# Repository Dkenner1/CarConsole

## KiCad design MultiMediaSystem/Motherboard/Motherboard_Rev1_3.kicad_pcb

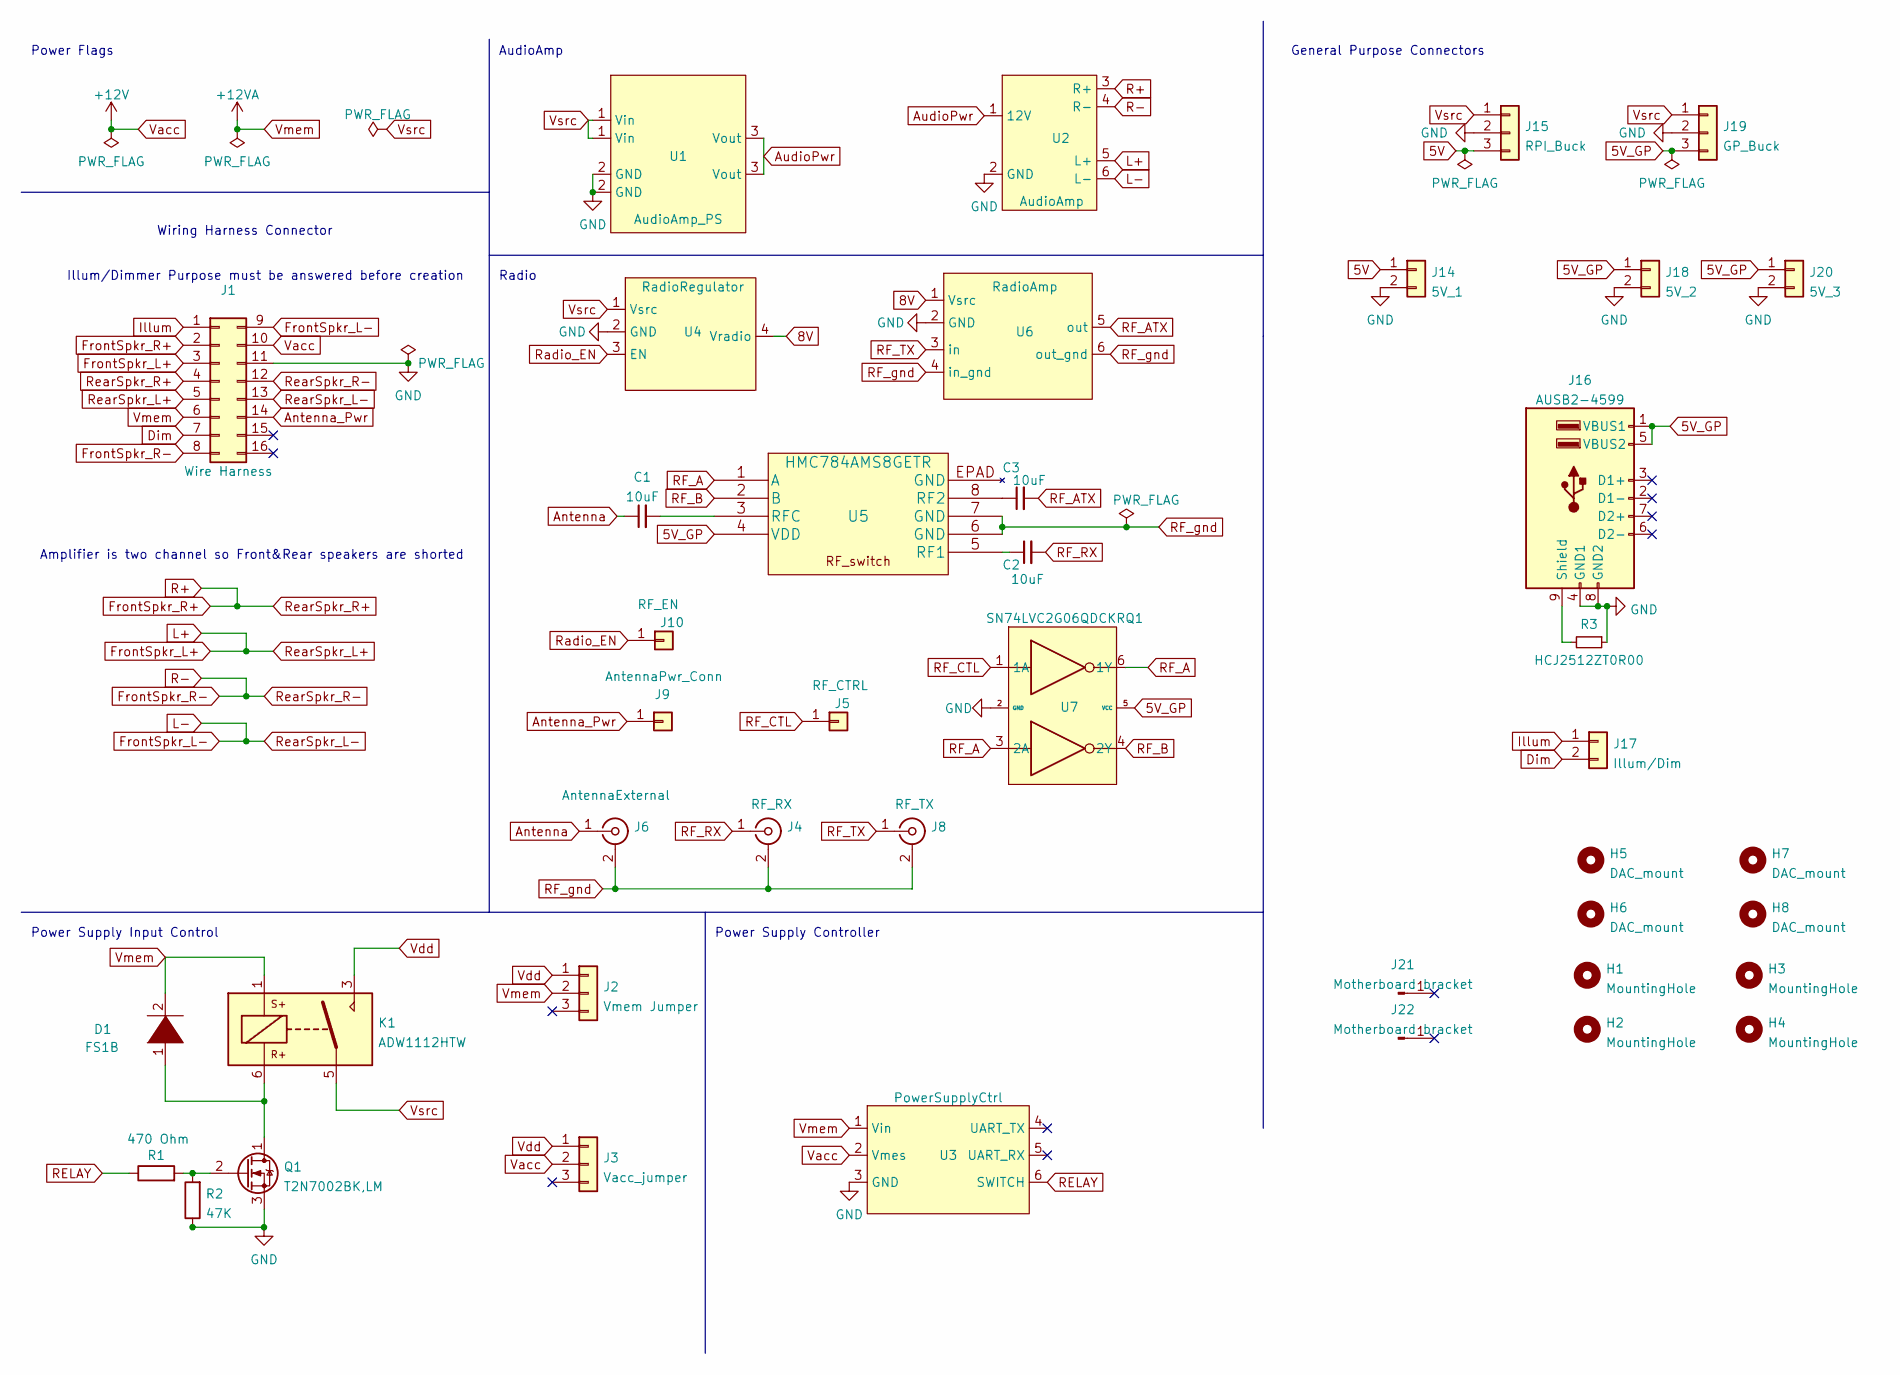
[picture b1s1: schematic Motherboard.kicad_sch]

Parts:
C1, C2, C3: 10uF; C_0603_1608Metric_Pad1.08x0.95mm_HandSolder
D1: FS1B; D_SOD-123F
H1, H2, H3, H4: MountingHole; RectangleSlot
H5, H6, H7, H8: DAC_mount; MountingHole_2.5mm_Pad
J1: Wire Harness; HeadUnit_Conn
J2: Vmem Jumper; PinHeader_1x03_P2.54mm_Vertical
J3: Vacc_jumper; PinHeader_1x03_P2.54mm_Vertical
J4: RF_RX; SMA_Amphenol_132134_Vertical
J5: RF_CTRL; PinSocket_1x01_P2.54mm_Vertical
J6: AntennaExternal; SubaruRadioJack
J8: RF_TX; SMA_Amphenol_132134_Vertical
J9: AntennaPwr_Conn; PinSocket_1x01_P2.54mm_Vertical
J10: RF_EN; PinSocket_1x01_P2.54mm_Vertical
J14: 5V_1; PinSocket_1x02_P2.54mm_Vertical
J15: RPI_Buck; 5V_Reg_Footprint_VertMnt
J16: AUSB2-4599; USB_A_Wuerth_61400826021_Horizontal_Stacked
J17: Illum/Dim; PinSocket_1x02_P2.54mm_Vertical
J18: 5V_2; PinSocket_1x02_P2.54mm_Vertical
J19: GP_Buck; 5V_Reg_Footprint_VertMnt
J20: 5V_3; PinSocket_1x02_P2.54mm_Vertical
J21: Motherboard bracket; MotherBoard_Bracket_2
J22: Motherboard bracket; MotherBoard_Bracket_1
K1: ADW1112HTW; Relay_1P1T_NO_10x24x18.8mm_Panasonic_ADW11xxxxW_THT
Q1: T2N7002BK,LM; SOT-23
R1: 470 Ohm; R_2010_5025Metric_Pad1.40x2.65mm_HandSolder
R2: 47K; R_2512_6332Metric_Pad1.40x3.35mm_HandSolder
R3: HCJ2512ZT0R00; R_2512_6332Metric_Pad1.40x3.35mm_HandSolder
U1: AudioAmp_PS
U2: AudioAmp
U3: PowerSupplyCtrl; PS_Controller
U4: RadioRegulator; PinHeader_1x04_P2.54mm_Vertical
U5: HMC784AMS8GETR
U6: RadioAmp
U7: SN74LVC2G06QDCKRQ1; SOT-363_SC-70-6_Handsoldering

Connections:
5V: J14.1, J15.3
5V_GP: J16.1 (VBUS1), J16.5 (VBUS2), J18.1, J19.3, J20.1, U5.4 (VDD), U7.5 (VCC)
8V: U4.4 (Vradio), U6.1 (Vsrc)
Antenna: C1.1, J6.1 (In)
Antenna_Pwr: J1.14, J9.1
AudioPwr: U1.3 (Vout), U2.1 (12V); also elsewhere on the board
Dim: J1.7, J17.2
FrontSpkr_L+: J1.3, J1.5, U2.5 (L+); also elsewhere on the board
FrontSpkr_L-: J1.9, J1.13, U2.6 (L-); also elsewhere on the board
FrontSpkr_R+: J1.2, J1.4, U2.3 (R+); also elsewhere on the board
FrontSpkr_R-: J1.8, J1.12, U2.4 (R-); also elsewhere on the board
GND: J1.11, J14.2, J15.2, J16.4 (GND1), J16.8 (GND2), J18.2, J19.2, J20.2, Q1.3 (S), R2.1, R3.1, U1.2 (GND), U2.2 (GND), U3.3 (GND), U4.2 (GND), U6.2 (GND), U7.2 (GND); also elsewhere on the board
Illum: J1.1, J17.1
unnamed: C1.2, U5.3 (RFC)
unnamed: C2.1, U5.5 (RF1)
unnamed: C3.1, U5.8 (RF2)
unnamed: D1.1 (K), K1.6, Q1.1 (D)
unnamed: J16.9 (Shield), R3.2
unnamed: Q1.2 (G), R1.2, R2.2
RELAY: R1.1, U3.6 (SWITCH)
RF_A: U5.1 (A), U7.3 (2A), U7.6 (1Y)
RF_ATX: C3.2, U6.5 (out)
RF_B: U5.2 (B), U7.4 (2Y)
RF_CTL: J5.1, U7.1 (1A)
RF_RX: C2.2, J4.1 (In)
RF_TX: J8.1 (In), U6.3 (in)
RF_gnd: J4.2 (Ext), J6.2 (Ext), J8.2 (Ext), U5.6 (GND), U5.7 (GND), U6.4 (in_gnd), U6.6 (out_gnd)
Radio_EN: J10.1, U4.3 (EN)
Vacc: J1.10, J3.2, U3.2 (Vmes)
Vdd: J2.1, J3.1, K1.3
Vmem: D1.2 (A), J1.6, J2.2, K1.1, U3.1 (Vin)
Vsrc: J15.1, J19.1, K1.5, U1.1 (Vin), U4.1 (Vsrc)

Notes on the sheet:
General Purpose Connectors
Power Flags
Illum/Dimmer Purpose must be answered before creation
Radio
Power Supply Input Control
Power Supply Controller
Wiring Harness Connector
AudioAmp
Amplifier is two channel so Front&Rear speakers are shorted

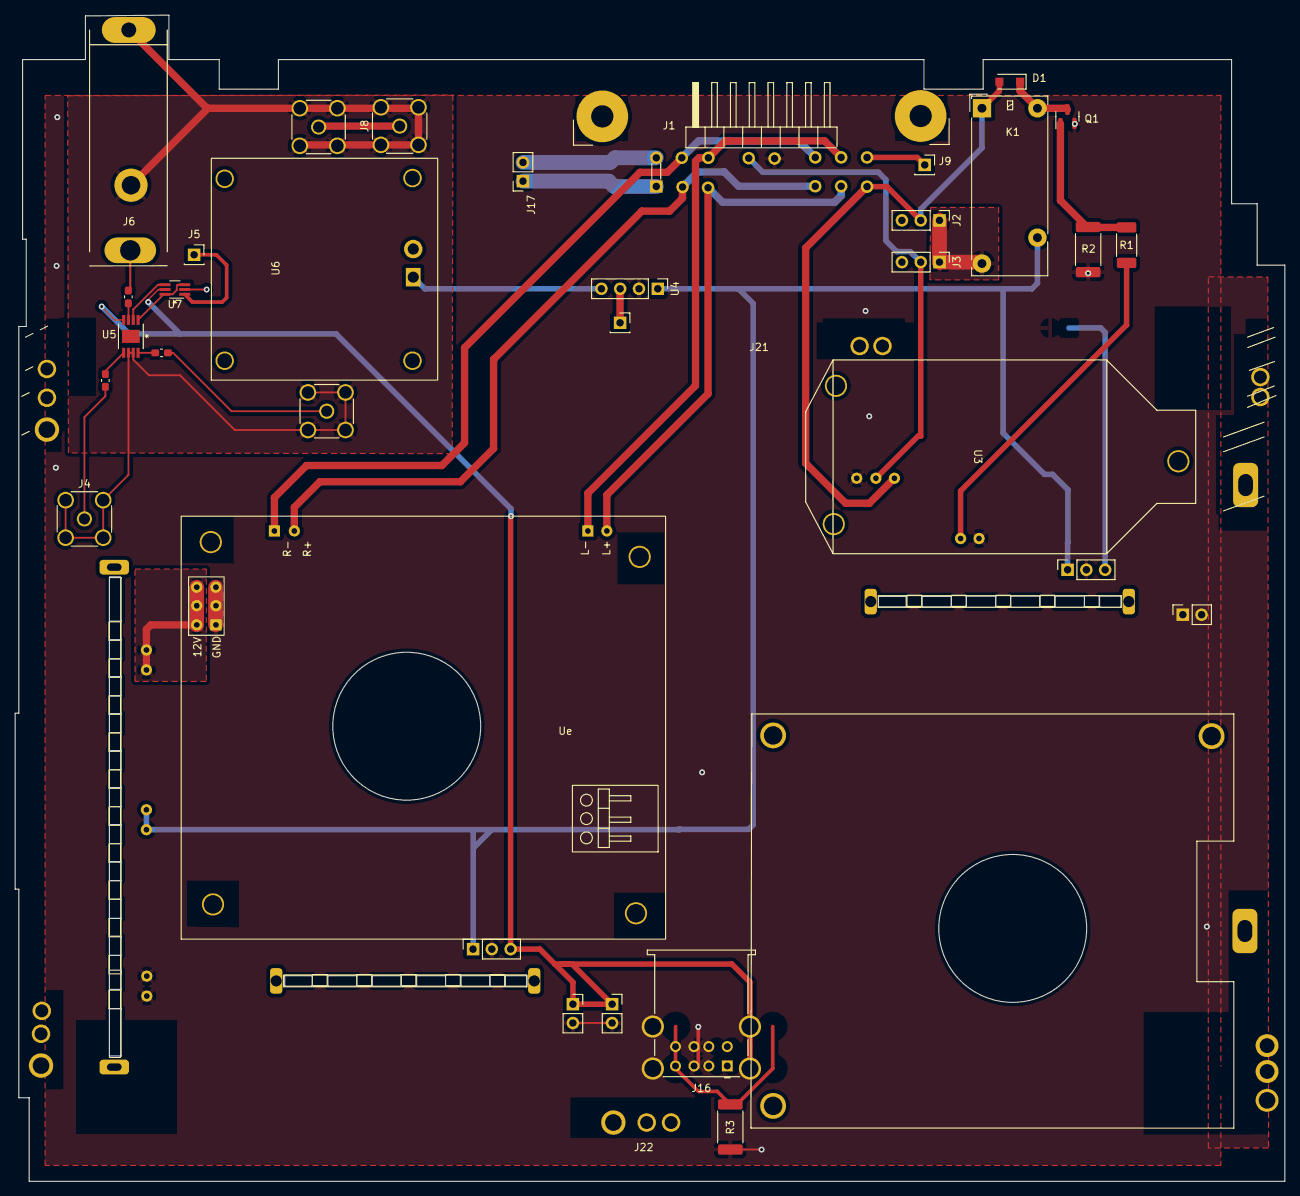
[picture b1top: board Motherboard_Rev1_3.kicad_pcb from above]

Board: 2 copper layers, 171.7 x 157.7 mm, 41 parts (0 on the bottom side), 32 nets.

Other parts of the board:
Ue: AudioAmp

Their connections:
AudioPwr: Ue.1 (12V); also elsewhere on the board
FrontSpkr_L+: Ue.5 (L+); also elsewhere on the board
FrontSpkr_L-: Ue.6 (L-); also elsewhere on the board
FrontSpkr_R+: Ue.3 (R+); also elsewhere on the board
FrontSpkr_R-: Ue.4 (R-); also elsewhere on the board
GND: Ue.2 (GND); also elsewhere on the board

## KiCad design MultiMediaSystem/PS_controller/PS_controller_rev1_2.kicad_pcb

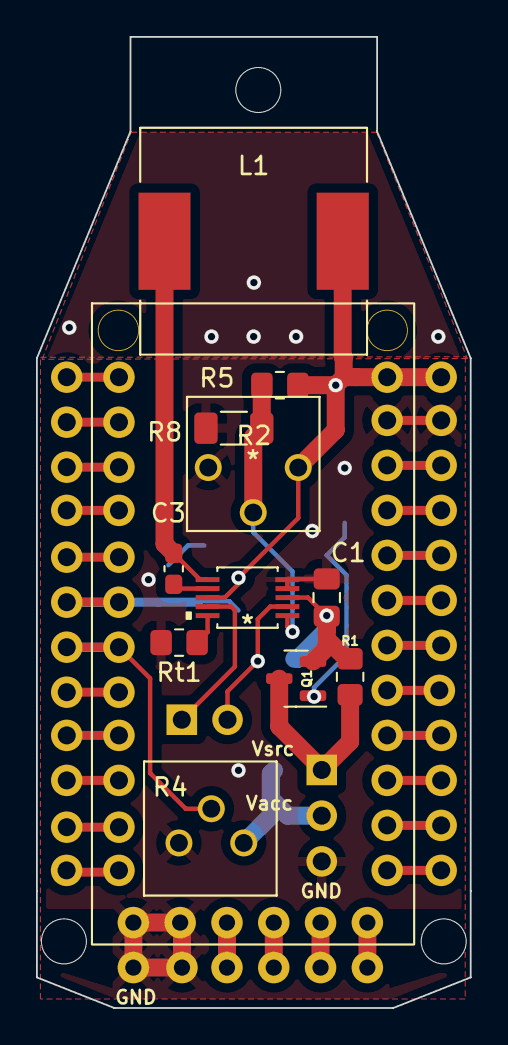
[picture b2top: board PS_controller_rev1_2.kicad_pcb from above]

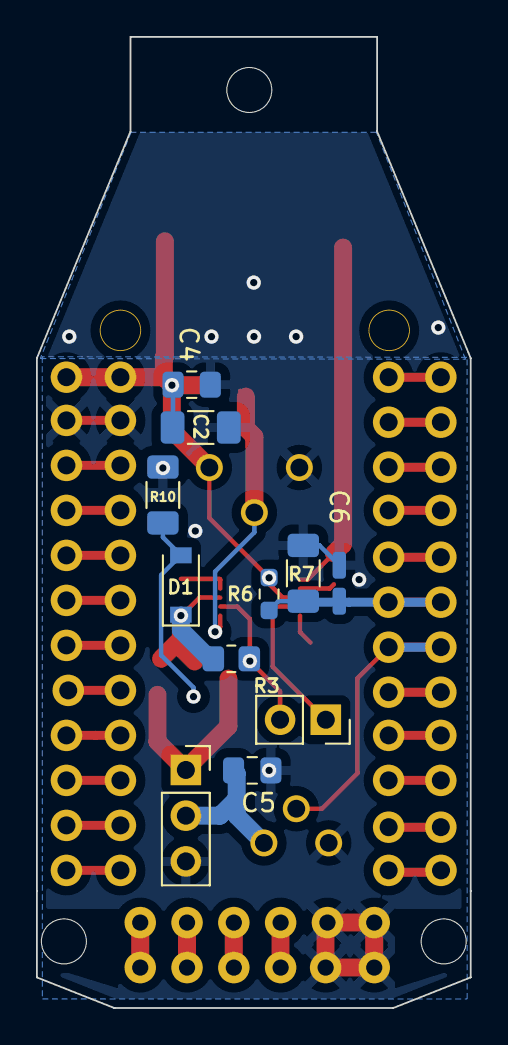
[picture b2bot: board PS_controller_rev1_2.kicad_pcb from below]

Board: 2 copper layers, 24.1 x 53.9 mm, 26 parts (11 on the bottom side), 14 nets.

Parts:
C1: 2.2uF; C_0805_2012Metric_Pad1.18x1.45mm_HandSolder
C2: 47u; C_1206_3216Metric_Pad1.33x1.80mm_HandSolder
C3: .22u; C_0603_1608Metric_Pad1.08x0.95mm_HandSolder
C4: 22p; C_0805_2012Metric_Pad1.18x1.45mm_HandSolder
C5: 47n; C_0805_2012Metric_Pad1.18x1.45mm_HandSolder
C6: 100n; C_0.64x0.4_Handsolder
D1: 25VBrkDwn; D_SOD-123
H1, H2, H3: MountingHole; MountingHole_2.5mm
J1: PWR_IN; PinSocket_1x03_P2.54mm_Vertical
J4: FET_CTRL; PinSocket_1x02_P2.54mm_Vertical
L1: 22u_CDRH127/LDNP-220MC; L_12x12mm_H8mm
Q1: AO3401A; SOT-23
R1, R3: JMP; R_0805_2012Metric_Pad1.20x1.40mm_HandSolder
R2: 1M_Pot; GF063P1
R4: CT6EW203_10K_4.545K; CT-6EW
R5: 1M; R_0805_2012Metric_Pad1.20x1.40mm_HandSolder
R6: 10K; R_0603_1608Metric_Pad0.98x0.95mm_HandSolder
R7, R10: 100K; R_1206_3216Metric_Pad1.30x1.75mm_HandSolder
R8: 316K; R_1206_3216Metric_Pad1.30x1.75mm_HandSolder
Rt1: 226k; R_0805_2012Metric_Pad1.20x1.40mm_HandSolder
T1: TrinketPro_5V; TrinketPro5V_partial
U1: LT3970HMS-TRPBF

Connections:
5.5V: C2.1, C4.1, L1.2, R2.1, R5.2, R6.2, T1.12 (VBAT), U1.8 (BD)
+12V: J1.1, Q1.3 (D), R1.1
Aref: C6.1, R6.1, R7.2, T1.18 (Ar)
Boost: C3.1, U1.7 (BOOST)
EN: J4.2, R3.1, U1.2 (EN)
FB: R2.2, R5.1, R8.2, U1.1 (FB/VOUT)
GND: C1.2, C2.2, C4.2, C5.2, C6.2, J1.3, R2.3, R4.3, R7.1, R8.1, R10.1, Rt1.2, T1.11 (GND), U1.4 (GND), U1.5 (GND)
unnamed: D1.2 (A), Q1.1 (G), R10.2
PG: J4.1, U1.9 (PG)
RT: Rt1.1, U1.10 (RT)
SW: C3.2, L1.1, U1.6 (SW)
Vacc: C5.1, J1.2, R4.1
Vin: C1.1, D1.1 (K), Q1.2 (S), R1.2, R3.2, U1.3 (VIN)
Vsense: R4.2, T1.19 (A0)

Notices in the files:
parts and their libraries:
Copyright 2021 Accelerated Designs. All rights reserved.
